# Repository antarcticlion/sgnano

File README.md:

# sgnano

**sgnano**（エスジーナノ）は、RP2350B のチップ 1 つで作る、昔ながらの操作感を持つパーソナルコンピュータです。
アナログ RGB の画面、PT8211 の 4 声ウェーブテーブル音源「Zack」、USB キーボード・マウス・ストレージを備え、
電源を入れるとファイラーが立ち上がり、その場で mruby・MicroPython・SG BASIC のプログラムを書いて走らせられます。

> いまは **α版** です。ファームウェアはバイナリ（UF2）で配り、ソースは後のリリースで公開する予定です。
> SGX の ABI は **5.x を凍結**しています（追加のみ）。文書も順次更新します。

*起動バナー。星は [`sgnano_remote`](https://github.com/antarcticlion/sgnano_remote) のアイコンです。*

## このリポジトリにあるもの

| フォルダ | 中身 |
|---|---|
| `docs/` | 3 言語のコーディングガイド、SGX の ABI、`Machine` の対応表、キー操作の早見表 |
| `samples/` | mruby・MicroPython・SG BASIC の見本（3 言語で同じものがそろったテスト用アプリ、ベンチマーク、デモ） |
| `sdk/sgx/` | C で外部実行ファイル（`.sgx`）を組むための SDK（ABI はα版の間に変わることがあります） |
| `apps/` | SGX の見本（`hello`）と CPU の計測 `cpubench`（α2 から。alpha2-2026.11.2 から 1 コア + 2 コア）。Doom と wav2mp3 のソースは別のリポジトリ（`sgnano_doomgeneric`・`sgnano_wav2mp3`） |
| `hardware/` | C ボードのガーバーと KiCad のプロジェクト（回路図・基板、α2 から） |
| `resources/bench/` | cpubench の負荷の曲（VGZ・MP3、CC BY-SA 4.0） |
| `LICENSES/` | ファームウェアと SGX に入っている外部の部品のライセンス文 |

## ハードウェア

- **CPU**: WeAct Studio RP2350B Core Board（Cortex-M33 x 2、302.4MHz で動かす）
- **メモリ**: SRAM 520KB、PSRAM 8MB、フラッシュ 16MB
- **画面**: R・G・B 各 5 ビットの R-2R ラダー DAC。15kHz / 24kHz / 31kHz の 12 通りのタイミング
- **音**: PT8211 x 4（1 チップに 1 声）。オペアンプで混ぜ、カットオフ 150kHz の LPF を通してラインアウトへ
- **入出力**: USB ホスト（フルスピード）、DIN MIDI、GPIO 8 本（PIO2 をユーザーに開放）、ADC

基板（C ボード、100 x 100mm）のガーバーと組み立てガイドは `hardware/c_board/` にあります。手はんだを前提にした高密度の実装です。

- [組み立てガイド（Markdown）](hardware/c_board/ASSEMBLY.md) / [PDF（26 ページ）](hardware/c_board/ASSEMBLY.pdf)
- [部品表（BOM）](hardware/c_board/C_BOARD_BOM.csv) / [配置（1 部品ごと）](hardware/c_board/C_BOARD_PLACEMENT.csv)

*C ボード（100 x 100mm）。RP2350B の Core Board、PT8211 x 4、DIN MIDI、VGA の DAC、GPIO のヘッダ。*

## ソフトウェア

- **ファイラー**: PC-98 の FD に倣った 2 列の一覧。テキストエディタ、日本語 IME、ZMODEM、コピー・移動
- **言語**: mruby 4.0.0、MicroPython 1.29.0、SG BASIC（3 言語の `Machine` は同じメソッドを持つ）
- **シェル**: csh のサブセット sgsh（VT220 の上位互換の端末）。OS/2 に倣うジョブ制御（`start`・`fg`・`bg`・`suspend`・`ends`・Ctrl-Z）で、同じ言語のプログラムを何本も同時に走らせられる
- **外部実行ファイル**: SGX（C で組み、PSRAM に読み込んで RTOS のタスクとして走らせる）。Core 0 にもサブタスクを起こせる（ABI 5.19）
- **画面**: テキスト面（80x30、Unicode、32 ビットの属性）・フレームバッファ（RGB555 / CLUT8 / CLUT4）・ローレゾ面（BG 2 面 + オブジェクト 128 個）
- **音**: 4 声のウェーブテーブル、SMF / SGT のシーケンサー、MP3 / OGG / WAV、VGM / VGZ（YM2151・YM2612・C352 など）

## 画面

実機の画面です（640x480。将棋・jumps・時計・CD は写真）。ほかにも `images/` にあります。

| | |
|---|---|
| <br>**ファイラー**。PC-98 の FD に倣った 2 列の一覧。 | <br>**表示の言語は 62**。欧州 34 言語を含みます。 |
| <br>**画面モード 3**。テキスト + ローレゾ + CLUT8 の FB。 | <br>**画面モード 7**。320x200x256 のプラズマとテキスト 25 行。 |
| <br>**jumps**（SGX の見本）。横スクロールのゲーム。 | <br>**フォントは 57,404 字**。色・線・回転・倍角を 1 画面で。 |
| <br>**将棋**（mruby の見本）。 | <br>**SGCALC**。mruby / MicroPython / SG BASIC のマクロ。 |
| <br>**CD のスペクトログラム**。44.1kHz ステレオ、128x128 を 2 面。 | <br>**時計**（F11）。NTP で合わせた日本時間。 |
| <br>**シェル sgsh**。csh のサブセット、組み込みコマンド 70 個。 | <br>**About**（F1 → → → →）。ビルド ID・ABI・フォント・言語数。 |

## パッチ 2（alpha2-2026.11.2）で変わったこと

前のパッチ（`alpha2-2026.11.1`、2026-11-23）から **92 のコミット**があり、内部の作りに大きく手が入っています。
新しい機能の多くは、「同じ 1 チップで、より多くを同時に、より滑らかに動かす」ための土台です。詳しくは Release のリリースノートを見てください。

### メモリ: 常駐していたコードを、使うときだけ SRAM に載せる（SRAM +32KB）

RP2350 の SRAM は 520KB しかなく、画面のライン、音、USB、言語の VM がそれを取り合います。これまでは、つながっていない機器のためのコードも
いつも SRAM に置いていました。パッチ 2 では次のコードを **使う間だけ SRAM に写して**走らせ、使い終わったら下ろします。

| まとまり | 載せるとき | 下ろすとき |
|---|---|---|
| ゲームパッド・マウス・ペンタブレット | 機器がつながったとき | 外れて 3 秒たったら |
| 光学ドライブ / FDD・ISO9660 | 光学ドライブ / FDD がつながったとき | 外れて 3 秒たったら |
| ファイラーの一部（一覧の受け口・読み込み・PNG の表示） | ファイラーが動いているとき | プログラムを走らせている間 |

- 何もつないでいないときの SRAM の空きは **173,515 B → 205,671 B（+32KB）** になりました。
- 光学ドライブ / FDD の受け場（4KB）と LAN の送受信の受け場（10.3KB）も、起動のときに取り置かず、機器がつながったときに取ります。
- SRAM が足りないときは、**フラッシュのまま遅く動きます**（止まったり壊れたりはしません）。遠隔コマンド `DYN` で、いまどこにあるかを見られます。

### 音: ドライバーも、鳴らすときだけ SRAM に

FM 音源（YM2151・OPL 系・OPN 系）、MP3 の復号、PCM 系の音源を、**曲が使うものだけ**空いた SRAM に載せるモジュールにしました。
固定の区画は 58KB → 15.9KB に縮み、音を鳴らしていないときの SRAM が大きく空きます。MP3 を鳴らしているときの負荷は **31% → 12%** になりました。
置き場は遠隔コマンド `MODS` で見られます。

### マルチタスク: Core 0 のサブタスクとジョブ制御

- SGX のプログラムが **Core 0 にもタスクを起こせます**（`task_create_core0` / `core_id`、SGX ABI 5.19）。Core 0 は画面を描く合間の空き時間で走らせます。
  3 言語にも `core_id` / `tasks` / `core_stat`。
- シェル sgsh に OS/2 風の **ジョブ制御**（`start`・`detach`・`fg`・`bg`・`suspend`・`ends`、Ctrl-Z）。mruby・MicroPython・SG BASIC のプログラムを何本も同時に走らせられます。

### 画面

- **起動バナー**を作り直しました。流れる星と回る「Ａ」を Core 0 のサブタスクで描くので、Core 1 が忙しくても止まりません。「Ａ」の 4 つのセルが別々のフレームで
  替わるティアリングと、免責の文の後ろの行が欠ける件を直しました。
- モード 2 の FB（2.4MB）を、要るときだけ取るようにしました（`fb_release` / `fb_acquire`、ABI 5.18）。シェルに入ると PSRAM へ返します。壁紙も出せます。
- SGX から 15kHz / 24kHz の画面も開けます（ABI 5.17）。
- ローレゾ面を決まった大きさ（パターン 16KB・パレット 8 本）で開く印 `SGX_MODE_LR_FIXED`（ABI 5.20）。

### 音楽 CD とプレイヤー

- 音楽 CD の再生画面の**文字のちらつきを直しました**。スペクトログラムの範囲は `r` で 1/1 → 1/2 → 1/4。
- `mplay` / `vgmplay` / ファイラーの VGM プレイヤーのスペクトログラムの直し・範囲の切り替え・周波数の目盛り・音量 200%。
- **C64 の SID の曲のプレイヤー `sidplay.sgx`**（新しい。WAV / MP3 への書き出しも）。

### そのほか

- `adcrec.sgx` が止まらなかった件、シェルの前景のプログラムへのキーの渡し方、UART のコンソールの長い行の文字落ち、Ruby のバックグラウンドのジョブを止めたときの
  HardFault などを直しました。JUMPS はパッドの上入力でもジャンプします。プログラムの実行中も画面の写し（Alt+PrintScreen）が撮れます。
- 表示の言語 62 言語の訳を直しました（キーの名前の誤訳など）。
- **SGX ABI は 5.16 → 5.20**。どれも表の末尾に足しただけで、**5.16 以前のプログラムはそのまま動きます**。

## sgnano magazine

α版を外の読者向けに紹介する読み物です。

- [第 1 号　ワンチップに「パソコン」を取り戻せ](docs/magazine/01_alpha_review.md)（2026-11-14、[誌面の PDF](docs/magazine/01_alpha_review.pdf)）
- [第 2 号　α版、出荷前夜](docs/magazine/02_alpha1_preview.md)（2026-11-17、[誌面の PDF](docs/magazine/02_alpha1_preview.pdf)）
- [第 3 号　α2、使ってみた](docs/magazine/03_alpha2_review.md)（2026-11-21、[誌面の PDF](docs/magazine/03_alpha2_review.pdf)）

## ダウンロードと書き込み

**最新リリースは [alpha2-2026.11.2](https://github.com/antarcticlion/sgnano/releases/tag/alpha2-2026.11.2) です。配布物は [Releases](https://github.com/antarcticlion/sgnano/releases) にあります。**

| 何を入れるか | ファイル |
|---|---|
| **最新ファームウェア**（S: とフォントを残して更新） | [alpha2-2026.11.2 の Release](https://github.com/antarcticlion/sgnano/releases/tag/alpha2-2026.11.2) / [ファーム UF2](https://github.com/antarcticlion/sgnano/releases/download/alpha2-2026.11.2/sgnano-alpha2-2026.11.2-firmware.uf2) |
| **S: の更新**（変わったファイル 29 本とインストーラ） | [S: の更新 zip](https://github.com/antarcticlion/sgnano/releases/download/alpha2-2026.11.2/sgnano-alpha2-2026.11.2-s-update.zip) |
| **α2 の一式**（初回。S: とフォントも入る） | [alpha2-2026.11 の Release](https://github.com/antarcticlion/sgnano/releases/tag/alpha2-2026.11) / [全体 UF2](https://github.com/antarcticlion/sgnano/releases/download/alpha2-2026.11/sgnano-alpha2-2026.11-full.uf2) / [IME の辞書](https://github.com/antarcticlion/sgnano/releases/download/alpha1-2026.11/sgnano-alpha1-2026.11-ime-dict.zip)（α1 と同じ） |
| **S: とフォント** | [後半 UF2](https://github.com/antarcticlion/sgnano/releases/download/alpha2-2026.11/sgnano-alpha2-2026.11-system-font.uf2) |

1. **初回**は α2 の全体 UF2 を、BOOTSEL で立ち上げた `RPI-RP2` へコピーします。**S: は初期化されます。**
2. そのあと、**最新ファームウェアの UF2（`alpha2-2026.11.2`）** をコピーします（ファームだけ更新。S: とフォントは残ります）。
3. **α1 や α2 から更新するとき**は、最新ファームウェアの UF2 をコピーしてください（S: とフォントはそのまま残ります）。
4. ファームを書いたら、下の手順で **S: の更新**を入れます（新しいプレイヤー・訳の直しなど。入れなくても新しいファームは動きます）。
5. 日本語の漢字変換には **IME の辞書**（`-ime-dict.zip`）が要ります。USB のドライブのルートに `SgnanoIME/` ごと置いてください（S: の 4MB には入りません）。
6. フォント ROM はファームと同じ版を使ってください。v1 の ROM では文字が出ません。

SHA-256 は各 Release の `SHA256SUMS` にあります。

### S: の更新の入れ方（alpha2-2026.11.2）

S:（内蔵フラッシュのシステムのドライブ、4MB）は空きが少ないので、**インストーラは USB メモリなどの外部のドライブに置いて使います**。
上書きする前のファイルの控えも、外部のドライブに取ります。新しいプログラムは新しいファームでないと読み込めないので、**先にファームを書いてください**。

1. `sgnano-alpha2-2026.11.2-s-update.zip` を PC で展開し、出てきた `sgnano-alpha2-2026.11.2-s-update` フォルダを丸ごと USB メモリ（FAT32・exFAT）に写します。
2. USB メモリを本体につなぎ、ファイラーでそのフォルダに入って **`install.rb` を Enter** で走らせます。
3. インストーラは次の順に進めます。
   1. 更新のファイル（S: のフォルダごとの ZIP）を USB メモリの作業フォルダへ一度展開し、大きさと CRC32 を確かめる。合わなければ何も書かずに止まる
   2. S: の空きが足りるかを確かめる
   3. **Y を押すと入れ始める**（ほかのキーでやめる）
   4. 上書きする S: のファイルを、USB メモリのそのフォルダの `backup/` に控える。控えられなければ S: に触らずに止まる
   5. S: へ入れ、入ったものの CRC32 を照らし合わせる。結果は画面と `S:/SystemLogs/install_alpha2-2026.11.2.txt` に残る
4. 入れている間は ESC を押さないでください。終わったら本体を再起動します（Shift+F12）。

**元に戻すとき**は、同じフォルダの **`restore.rb` を Enter** で走らせます。いちばん新しい控えから書き戻し、更新で新しく入ったファイルは消します。

入るもの（29 本）:

| S: のフォルダ | ファイル |
|---|---|
| `S:/bin/` | `mplay.sgx`・`vgmplay.sgx`（スペクトログラムの直しなど）、`sidplay.sgx`（新しい） |
| `S:/sbin/` | `ps.sgx`（Core 0 のタスクとコアの列） |
| `S:/SystemFiles/Locale/` | `locales.7z`（62 言語の訳の直し） |
| `S:/testapp/` | `adcrec.sgx`・`jumps.*`（5 本）・`stress.sgx`・`mode0`〜`mode6.sgx`・`mode1_vgm`〜`mode6_vgm.sgx`・`mode6_15k.sgx`・`mode6_24k.sgx`（新しい） |

## CPU の計測（cpubench、alpha2-2026.11.2）

[`apps/cpubench`](apps/cpubench/) で、画面モードと音楽の負荷の下で Dhrystone 2.1 と Linpack（n = 100）を測った結果です
（clk_sys 302.4 MHz、1 つ 5 秒、データとスタックは SRAM。2026-11-28、alpha2-2026.11.2）。かっこの中は α2（2026-11-21）の値です。

**1 コア（Core 1）**

| 画面 | 音楽 | DMIPS | 単精度 MFLOPS | 倍精度 MFLOPS | 曲の負荷 |
|---|---|---:|---:|---:|---:|
| モード 0（表示なし） | なし | 419.8（410.9） | 60.50（59.61） | 7.23（7.13） | 0% |
| モード 0 | MP3 | **350.9**（263.3） | **50.41**（39.24） | n/a（4.60） | **12%**（31%） |
| モード 0 | VGM（YM2151 + C352） | 147.9（155.0） | 24.27（24.94） | **2.73**（n/a） | 60%（57%） |
| モード 2（テキスト + RGB555 の FB） | なし | 116.2（116.8） | 16.86（16.95） | 2.00（2.02） | 0% |
| モード 2 | MP3 | **72.6**（2.2） | **10.60**（0.49） | n/a（0.00） | **21%**（111%） |
| モード 5（テキスト + ローレゾ） | なし | 416.1（410.6） | 59.97（59.56） | 7.18（7.15） | 0% |
| モード 6（ローレゾだけ） | MP3 | **347.4**（264.3） | n/a（39.41） | n/a | **12%**（31%） |
| モード 7（テキスト + 320x200 のビットマップ） | なし | **417.9**（358.1） | **60.32**（52.12） | n/a（6.55） | 0% |

**2 コア（Core 1 + Core 0 のサブタスク）**

| 画面 | 音楽 | DMIPS | 単精度 MFLOPS |
|---|---|---:|---:|
| モード 0 | なし | 669.4 | 105.61 |
| モード 6 | なし | 517.1 | 78.49 |
| モード 7 | なし | 611.1 | n/a |

- MP3 の復号が SRAM に載るモジュールになり、MP3 を鳴らしながらの計算が大きく伸びました（FB を出すモード 2 で 2.2 → 72.6 DMIPS）。
- 画面の乱れ（fifo_stall）は、全部の組み合わせで 0 でした（α2 では FB のモードで 2〜38）。
- n/a は、SRAM に必要な連続した空きが無くて測れなかった組み合わせです。MP3 の復号が SRAM を使うぶん、MP3 を鳴らしながらの倍精度は測れなくなりました。
  2 コアの倍精度は 163KB の連続した SRAM が要るので測れません。
- FB を出すモードでは、画面の取得がメモリの帯域を使うぶん遅くなります。

**サウンドフォント（SF2）は入っていません。** ファームの SMF 再生は内蔵の音源（4 声のウェーブテーブル）で鳴るので要りません。
`smf2vgm.sgx`（MIDI → VGM / VGZ）を使うときだけ、[MuseScore_General.sf2](https://ftp.osuosl.org/pub/musescore/soundfont/MuseScore_General/MuseScore_General.sf2)（約 83MB、MIT）を落として、
USB メモリの `<ドライブ>:/SoundFonts/` に置いてください（S: の 4MB には入りません）。`.sf3` は読みません。
変換した VGM / VGZ を配るときは、MuseScore General の著作権表示と MIT の許諾文を添えてください。

## 文書

入口は [`docs/README.md`](docs/README.md) です。

## 関連プロジェクト

### このプロジェクトのリポジトリ

| リポジトリ | 中身 | ライセンス |
|---|---|---|
| [`antarcticlion/sgnano`](https://github.com/antarcticlion/sgnano) | このリポジトリ。ファームのバイナリ（UF2）・文書・見本・SGX の SDK・基板データ | バイナリは無償配布、SDK と見本は MIT、文書は CC BY-SA 4.0、基板は CERN-OHL-P-2.0 |
| [`antarcticlion/EmbFont16`](https://github.com/antarcticlion/EmbFont16) | フォント ROM の形式・ビルダー（v2.0、57,404 字） | MIT（字形は GNU Unifont などのライセンス） |
| [`antarcticlion/sgnano_remote`](https://github.com/antarcticlion/sgnano_remote) | PC からファイルを管理する道具（v0.1.0。**デバッグプローブが必須**。UART の遠隔コマンドと ZMODEM で話す。起動バナーの星はこのアイコン） | MIT |
| [`antarcticlion/sgnano_doomgeneric`](https://github.com/antarcticlion/sgnano_doomgeneric) | Doom（`DOOM.SGX`。doomgeneric と Freedoom） | GPL-2.0 |
| [`antarcticlion/sgnano_wav2mp3`](https://github.com/antarcticlion/sgnano_wav2mp3) | VGM / VGZ を WAV / MP3 に書き出す `wav2mp3.sgx`（LAME） | LGPL-2.0-or-later |
| [`antarcticlion/sgnano_povray`](https://github.com/antarcticlion/sgnano_povray) | POV-Ray 3.7 の `povray.sgx`（ファームにリンクしない独立した SGX） | AGPL-3.0-or-later |

### 使っている外部のソフトウェア

| 部品 | 使い道 | ライセンス | 上流 |
|---|---|---|---|
| mruby 4.0.0 | Ruby | MIT | <https://github.com/mruby/mruby> |
| MicroPython 1.29.0 | Python | MIT | <https://github.com/micropython/micropython> |
| doomgeneric | Doom の本体 | GPL-2.0 | <https://github.com/ozkl/doomgeneric> |
| LAME 3.100 | MP3 の符号化（`wav2mp3`） | LGPL-2.0-or-later | <https://lame.sourceforge.io/> |
| Raspberry Pi Pico SDK 2.2.0 | 土台の SDK | BSD-3-Clause | <https://github.com/raspberrypi/pico-sdk> |
| TinyUSB | USB ホスト | MIT | <https://github.com/hathach/tinyusb> |
| lwIP 2.2 | TCP/IP | BSD-3-Clause | <https://savannah.nongnu.org/projects/lwip/> |
| Mbed TLS 3.6.2 | TLS 1.2・SHA | Apache-2.0 | <https://github.com/Mbed-TLS/mbedtls> |
| ymfm | VGM の FM 音源 | BSD-3-Clause | <https://github.com/aaronsgiles/ymfm> |
| libvgm | VGM の PCM 音源 | BSD-3-Clause | <https://github.com/ValleyBell/libvgm> |
| minimp3 | MP3 の解読 | CC0-1.0 | <https://github.com/lieff/minimp3> |
| stb_vorbis / stb_image | OGG の解読、PNG / JPEG / GIF の解読 | MIT / Public Domain | <https://github.com/nothings/stb> |
| miniz | gzip（VGZ）の展開 | MIT | <https://github.com/richgel999/miniz> |
| libbzip2 1.0.8 | bzip2 | BSD 系 | <https://sourceware.org/bzip2/> |
| LZMA SDK 26.06 | LZMA・xz・7z | Public Domain | <https://7-zip.org/sdk.html> |
| Onigmo 6.2.0 | Ruby の正規表現 | BSD-2-Clause | <https://github.com/k-takata/Onigmo> |
| GNU Unifont | フォントの字形 | SIL OFL 1.1 | <https://unifoundry.com/unifont/> |
| Unicode のデータ（Unihan） | IME の倉頡の表 | Unicode License V3 | <https://www.unicode.org/license.txt> |

全部の一覧とライセンス文は [`LICENSES/README.md`](LICENSES/README.md) にあります。

## 免責事項

sgnano（ファームウェア・SDK・見本・文書・基板のデータを含む）は**「現状のまま」**提供します。
明示か黙示かを問わず、商品性・特定の目的への適合性・権利を侵害していないことを含め、いかなる保証もしません。
sgnano を使ったこと、または使えなかったことによって生じたいかなる損害（データの消失、機器の故障、
ほかの機器・媒体への損害を含む）についても、作者は責任を負いません。

- α版です。ファイルの書き込みを伴う操作の前には、大切なデータのバックアップを取ってください。
- 基板の製作・改造・電源の扱いは、ご自身の責任で行ってください。
- 不具合の報告は歓迎しますが、対応や修正を約束するものではありません。

## ライセンス

詳しくは [`LICENSE`](LICENSE) を見てください。本体のファイラーで表示しているライセンスとクレジットと同じ内容も、そこに載せています。

- ファームウェアは**フリーソフトウェア**（無償で使える。バイナリの配布）として公開します。
- ファームウェアに入っている外部の部品のライセンス文は `LICENSES/` にあります。一覧は [`LICENSES/README.md`](LICENSES/README.md)。
- Doom（GPL-2.0）と wav2mp3（LGPL-2.0-or-later、LAME）のソースとビルドの手順は、別のリポジトリ [`sgnano_doomgeneric`](https://github.com/antarcticlion/sgnano_doomgeneric) と [`sgnano_wav2mp3`](https://github.com/antarcticlion/sgnano_wav2mp3) にあります。
- `samples/` の見本のプログラムは **MIT** です（`samples/LICENSE`。`neon_c/` も MIT）。`samples/sound/WTF4CH.mid` は **CC0** です（`samples/sound/LICENSE`）。
- `sdk/sgx/` は **MIT**、`apps/hello` は **CC0**、`docs/` は **CC BY-SA 4.0**、`hardware/`（ガーバー）は **CERN-OHL-P-2.0** です（それぞれのフォルダの `LICENSE`）。

---

Copyright (c) 2026 antarcticlion（南極獅子）。詳しくは [`LICENSE`](LICENSE) を見てください。

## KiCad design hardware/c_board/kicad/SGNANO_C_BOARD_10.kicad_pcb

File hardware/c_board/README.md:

# SGNANO C ボード Rev1.0

- **組み立てガイド**: [Markdown](ASSEMBLY.md) / [PDF（26 ページ）](ASSEMBLY.pdf)
- **部品表（BOM）**: [C_BOARD_BOM.csv](C_BOARD_BOM.csv)（グループ版、48 行）
- **配置**: [C_BOARD_PLACEMENT.csv](C_BOARD_PLACEMENT.csv)（1 部品ごとの基準番号・座標・面・実装方法）
- **ガーバー**: [SGNANO_C_BOARD_10.zip](SGNANO_C_BOARD_10.zip)（Rev1.0、2026-10-28 出力。シルクの `OCT/2027` は `2026-10-28` の誤植）
- **KiCad のプロジェクト**: [kicad/](kicad/)（回路図 `SGNANO_C_BOARD_10.kicad_sch`・基板 `.kicad_pcb`・プロジェクト `.kicad_pro`・配線の決まり `.rules`。題字の枠の版 R01.001、2026-11-21。α2 から）
- **ライセンス**: 基板データは CERN-OHL-P-2.0（[`../LICENSE`](../LICENSE)）。文書は CC BY-SA 4.0（[`../../docs/LICENSE`](../../docs/LICENSE)）

基板は 100 x 100mm、手はんだを前提にした高密度の実装です。対象は C ボード Rev1.0 です。

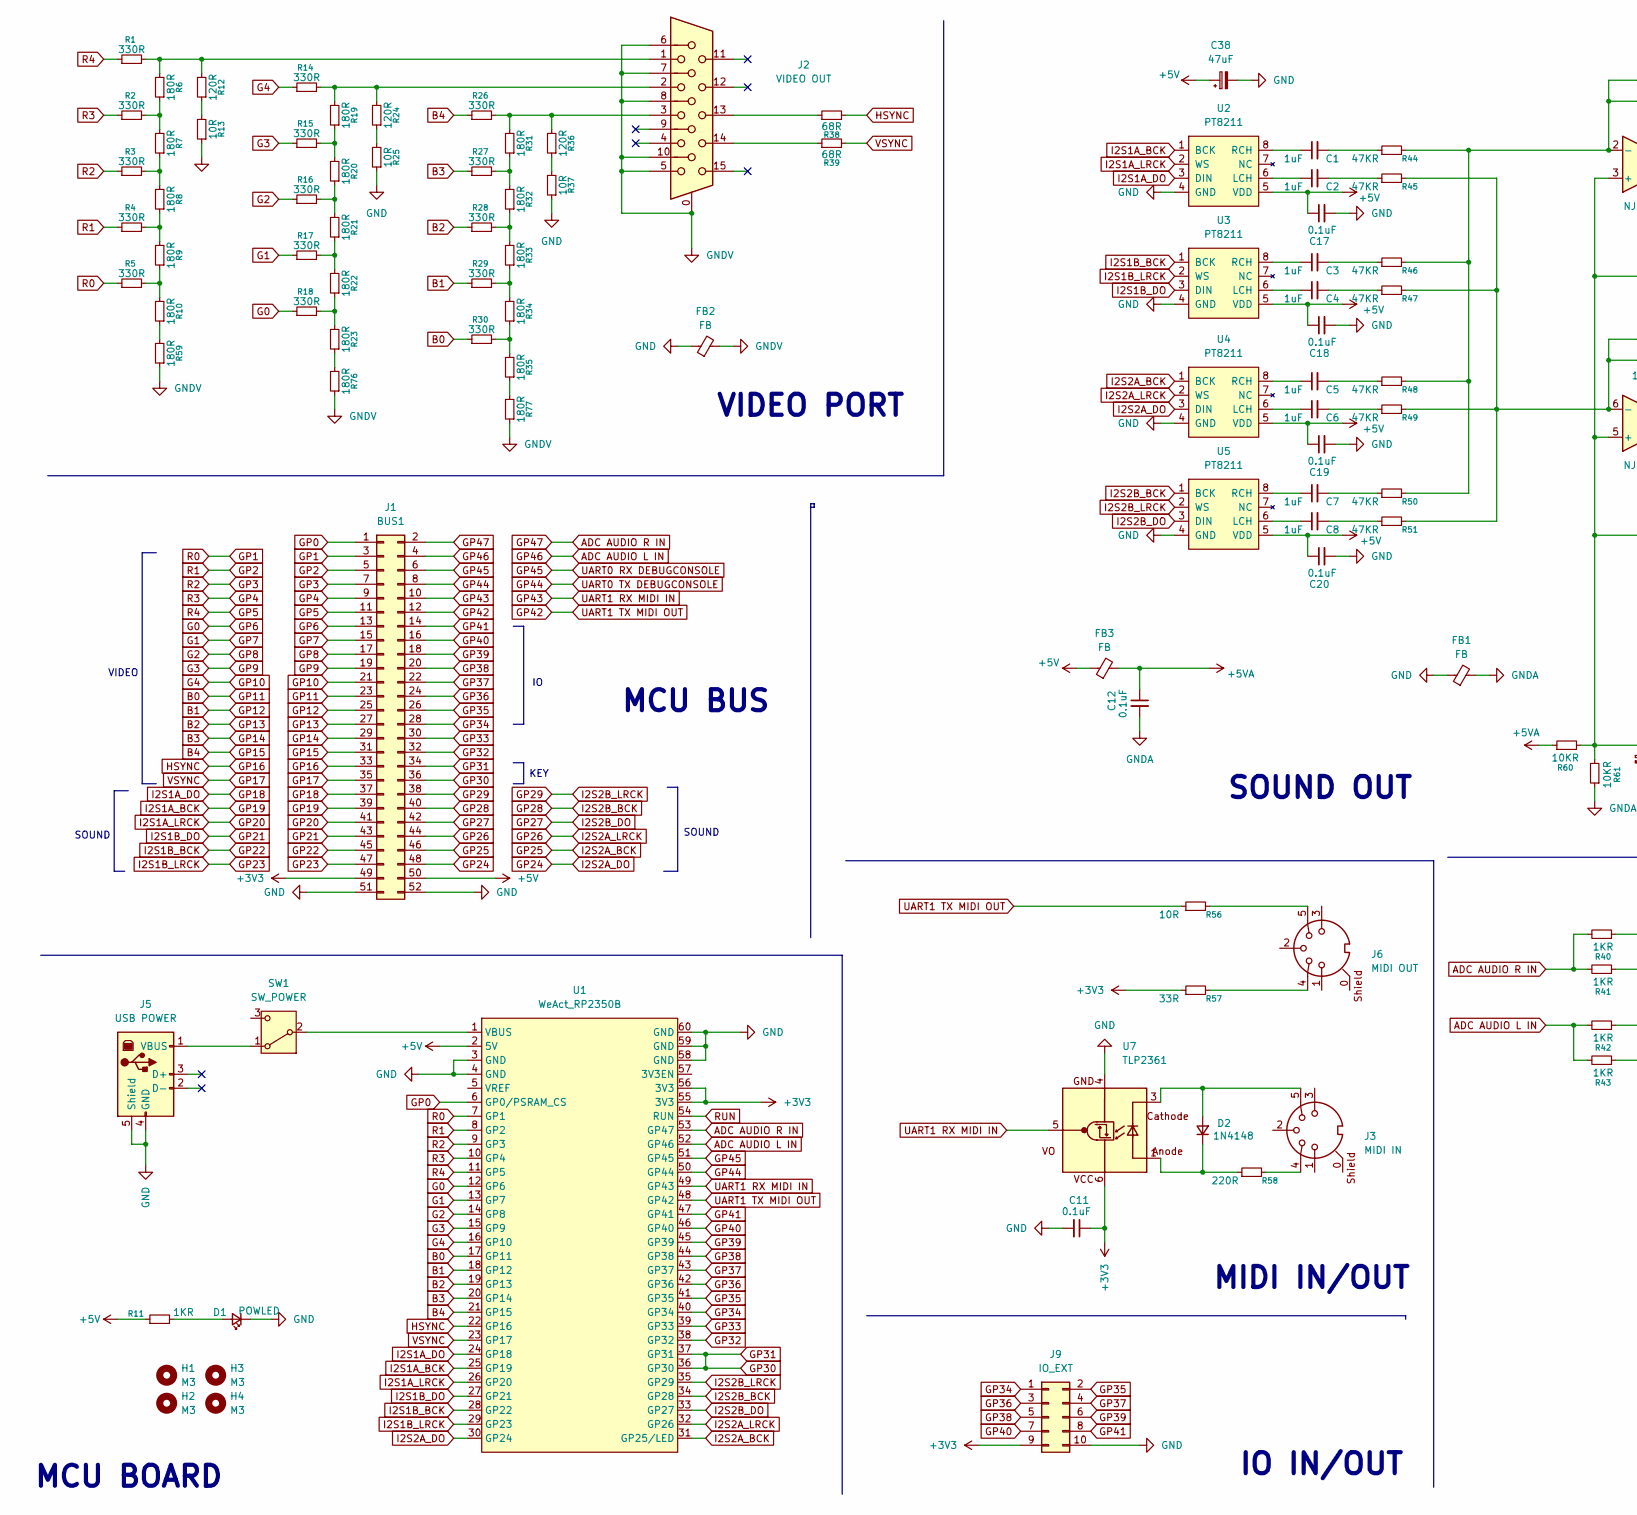
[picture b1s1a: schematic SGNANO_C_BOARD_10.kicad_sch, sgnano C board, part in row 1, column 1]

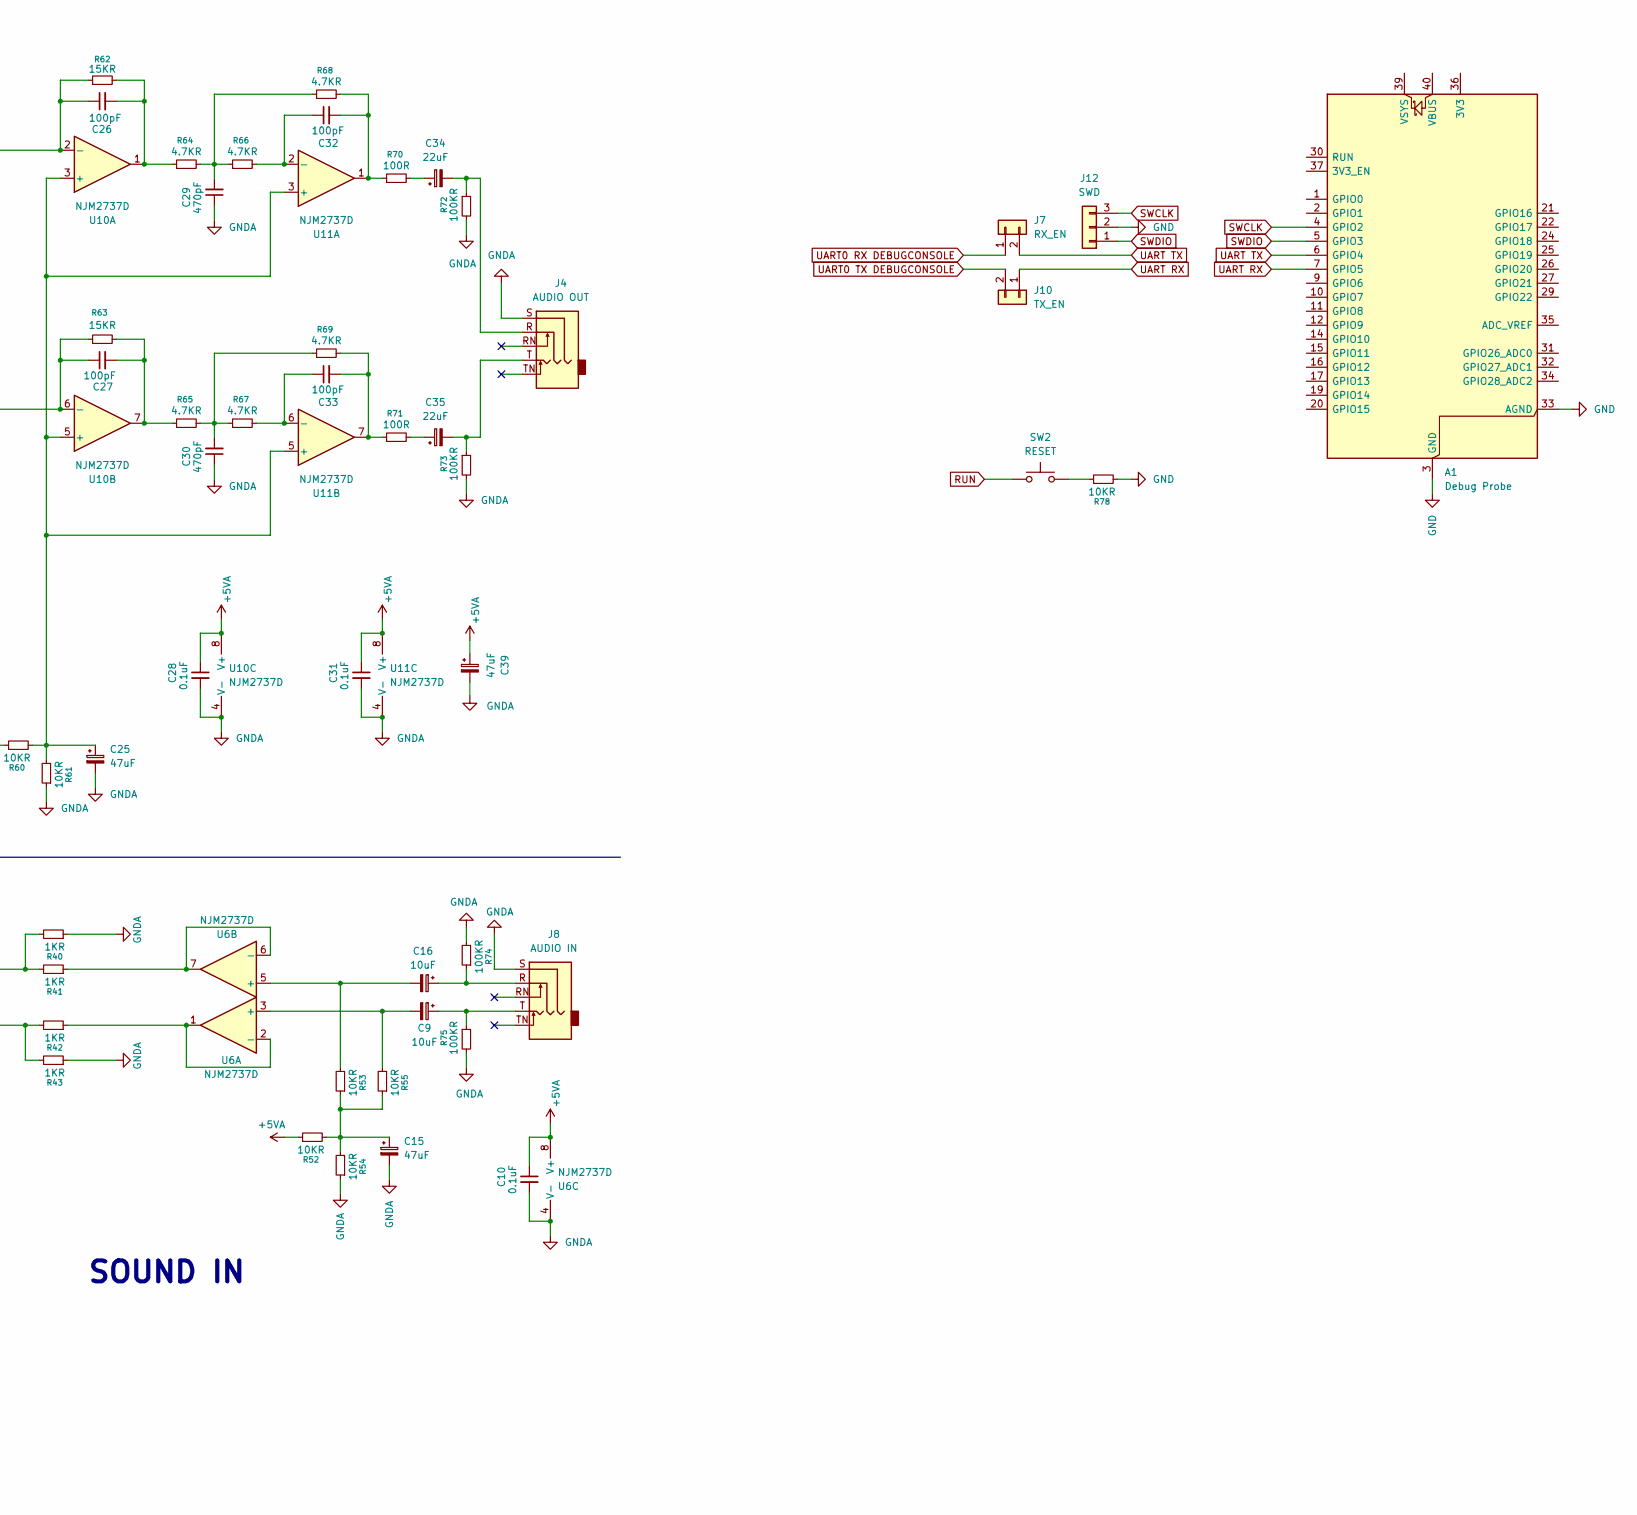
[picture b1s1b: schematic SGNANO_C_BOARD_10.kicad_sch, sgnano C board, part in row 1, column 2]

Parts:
A1: Debug Probe; RaspberryPi_Pico_Common_Unspecified
C1, C2, C3, C4, C5, C6, C7, C8: 1uF; C_Rect_L7.2mm_W5.5mm_P5.00mm_FKS2_FKP2_MKS2_MKP2
C9, C16: 10uF; CP_Radial_D5.0mm_P2.50mm
C10, C11, C12, C17, C18, C19, C20, C28, C31: 0.1uF; C_Disc_D5.0mm_W2.5mm_P5.00mm
C15, C25, C38, C39: 47uF; CP_Radial_D5.0mm_P2.50mm
C26, C27, C32, C33: 100pF; C_Disc_D5.0mm_W2.5mm_P5.00mm
C29, C30: 470pF; C_Disc_D5.0mm_W2.5mm_P5.00mm
C34, C35: 22uF; CP_Radial_D5.0mm_P2.50mm
D1: POWLED; LED_D3.0mm
D2: 1N4148; D_A-405_P7.62mm_Horizontal
FB1, FB2, FB3: FB; D_A-405_P2.54mm_Vertical_AnodeUp
H1, H2, H3, H4: M3; MountingHole_3.2mm_M3
J1: BUS1; PinHeader_2x26_P2.54mm_Vertical
J2: VIDEO OUT; DB_15F-VGA_L_NOSILK
J3: MIDI IN; DIN_8_PCB
J4: AUDIO OUT; PJ-3900-04
J5: USB POWER; USB_B_Lumberg_2411_02_Horizontal
J6: MIDI OUT; DIN_8_PCB
J7: RX_EN; PinHeader_1x02_P2.54mm_Vertical
J8: AUDIO IN; PJ-3900-04
J9: IO_EXT; IDC-Header_2x05_P2.54mm_Horizontal
J10: TX_EN; PinHeader_1x02_P2.54mm_Vertical
J12: SWD; PinHeader_1x03_P2.54mm_Vertical
R1, R2, R3, R4, R5, R14, R15, R16, R17, R18, R26, R27, R28, R29, R30: 330R; R_Axial_DIN0204_L3.6mm_D1.6mm_P2.54mm_Vertical
R6, R7, R8, R9, R10, R19, R20, R21, R22, R23, R31, R32, R33, R34, R35, R59, R76, R77: 180R; R_Axial_DIN0204_L3.6mm_D1.6mm_P2.54mm_Vertical
R11, R40, R41, R42, R43: 1KR; R_Axial_DIN0204_L3.6mm_D1.6mm_P2.54mm_Vertical
R12, R24, R36: 120R; R_Axial_DIN0204_L3.6mm_D1.6mm_P2.54mm_Vertical
R13, R25, R37, R56: 10R; R_Axial_DIN0204_L3.6mm_D1.6mm_P2.54mm_Vertical
R38, R39: 68R; R_Axial_DIN0204_L3.6mm_D1.6mm_P2.54mm_Vertical
R44, R45, R46, R47, R48, R49, R50, R51: 47KR; R_Axial_DIN0204_L3.6mm_D1.6mm_P2.54mm_Vertical
R52, R53, R54, R55, R60, R61, R78: 10KR; R_Axial_DIN0204_L3.6mm_D1.6mm_P2.54mm_Vertical
R57: 33R; R_Axial_DIN0204_L3.6mm_D1.6mm_P2.54mm_Vertical
R58: 220R; R_Axial_DIN0204_L3.6mm_D1.6mm_P2.54mm_Vertical
R62, R63: 15KR; R_Axial_DIN0204_L3.6mm_D1.6mm_P2.54mm_Vertical
R64, R65, R66, R67, R68, R69: 4.7KR; R_Axial_DIN0204_L3.6mm_D1.6mm_P2.54mm_Vertical
R70, R71: 100R; R_Axial_DIN0204_L3.6mm_D1.6mm_P2.54mm_Vertical
R72, R73, R74, R75: 100KR; R_Axial_DIN0204_L3.6mm_D1.6mm_P2.54mm_Vertical
SW1: SW_POWER; 2MS1T1B4M7QES
SW2: RESET; SW_SPST_Omron_B3F-315x_Angled
U1: WeAct_RP2350B
U2, U3, U4, U5: PT8211; SOP-8_3.9x4.9mm_P1.27mm
U6, U10, U11: NJM2737D; DIP-8_W7.62mm_Socket
U7: TLP2361; SO-5_4.4x3.6mm_P1.27mm

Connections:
+3V3: C11.1, J1.49, J9.9, R57.1, U1.55 (3V3), U1.56 (3V3), U7.6 (VDD)
+5V: C17.1, C18.1, C19.1, C20.1, C38.1, FB3.1, J1.50, R11.1, U1.2 (5V), U2.5 (VDD), U3.5 (VDD), U4.5 (VDD), U5.5 (VDD)
+5VA: C10.1, C12.1, C28.1, C31.1, C39.1, FB3.2, R52.1, R60.1, U6.8 (V+), U10.8 (V+), U11.8 (V+)
ADC AUDIO L IN: J1.4, R42.2, R43.2, U1.52 (GP46)
ADC AUDIO R IN: J1.2, R40.2, R41.2, U1.53 (GP47)
B0: J1.23, R30.1, U1.17 (GP11)
B1: J1.25, R29.1, U1.18 (GP12)
B2: J1.27, R28.1, U1.19 (GP13)
B3: J1.29, R27.1, U1.20 (GP14)
B4: J1.31, R26.1, U1.21 (GP15)
G0: J1.13, R18.1, U1.12 (GP6)
G1: J1.15, R17.1, U1.13 (GP7)
G2: J1.17, R16.1, U1.14 (GP8)
G3: J1.19, R15.1, U1.15 (GP9)
G4: J1.21, R14.1, U1.16 (GP10)
GND: A1.3 (GND), A1.8 (GND), A1.13 (GND), A1.18 (GND), A1.23 (GND), A1.28 (GND), A1.33 (AGND), A1.38 (GND), C11.2, C17.2, C18.2, C19.2, C20.2, C38.2, D1.1 (K), FB1.1, FB2.1, J1.51, J1.52, J5.4 (GND), J5.5 (Shield), J9.10, J12.2, R13.1, R25.1, R37.1, R78.2, U1.3 (GND), U1.4 (GND), U1.58 (GND), U1.59 (GND), U1.60 (GND), U2.4 (GND), U3.4 (GND), U4.4 (GND), U5.4 (GND), U7.4 (GND)
GNDA: C10.2, C12.2, C15.2, C25.2, C28.2, C29.1, C30.1, C31.2, C39.2, FB1.2, J4.S, J8.S, R40.1, R43.1, R54.1, R61.1, R72.2, R73.2, R74.2, R75.2, U6.4 (V-), U10.4 (V-), U11.4 (V-)
GNDV: FB2.2, J2.0, J2.5, J2.6, J2.7, J2.8, J2.10, R59.1, R76.1, R77.1
GP0: J1.1, U1.6 (GP0/PSRAM_CS)
GP1: J1.3, R5.1, U1.7 (GP1)
GP2: J1.5, R4.1, U1.8 (GP2)
GP3: J1.7, R3.1, U1.9 (GP3)
GP4: J1.9, R2.1, U1.10 (GP4)
GP5: J1.11, R1.1, U1.11 (GP5)
GP16: J1.33, R38.2, U1.22 (GP16)
GP17: J1.35, R39.2, U1.23 (GP17)
GP18: J1.37, U1.24 (GP18), U2.3 (DIN)
GP19: J1.39, U1.25 (GP19), U2.1 (BCK)
GP20: J1.41, U1.26 (GP20), U2.2 (WS)
GP21: J1.43, U1.27 (GP21), U3.3 (DIN)
GP22: J1.45, U1.28 (GP22), U3.1 (BCK)
GP23: J1.47, U1.29 (GP23), U3.2 (WS)
GP24: J1.48, U1.30 (GP24), U4.3 (DIN)
GP25: J1.46, U1.31 (GP25/LED), U4.1 (BCK)
GP26: J1.44, U1.32 (GP26), U4.2 (WS)
GP27: J1.42, U1.33 (GP27), U5.3 (DIN)
GP28: J1.40, U1.34 (GP28), U5.1 (BCK)
GP29: J1.38, U1.35 (GP29), U5.2 (WS)
GP30: J1.34, J1.36, U1.36 (GP30), U1.37 (GP31)
GP32: J1.32, U1.38 (GP32)
GP33: J1.30, U1.39 (GP33)
GP34: J1.28, J9.1, U1.40 (GP34)
GP35: J1.26, J9.2, U1.41 (GP35)
GP36: J1.24, J9.3, U1.42 (GP36)
GP37: J1.22, J9.4, U1.43 (GP37)
GP38: J1.20, J9.5, U1.44 (GP38)
GP39: J1.18, J9.6, U1.45 (GP39)
GP40: J1.16, J9.7, U1.46 (GP40)
GP41: J1.14, J9.8, U1.47 (GP41)
GP42: J1.12, R56.1, U1.48 (GP42)
GP43: J1.10, U1.49 (GP43), U7.5 (VO)
GP44: J1.8, J10.2, U1.50 (GP44)
GP45: J1.6, J7.1, U1.51 (GP45)
unnamed: C1.2, R44.1
unnamed: C2.2, R45.1
unnamed: C3.2, R46.1
unnamed: C4.2, R47.1
unnamed: C5.2, R48.1
unnamed: C6.2, R49.1
unnamed: C7.2, R50.1
unnamed: C8.2, R51.1
unnamed: C9.1, J8.T, R75.1
unnamed: C15.1, R52.2, R53.1, R54.2, R55.1
unnamed: C16.1, J8.R, R74.1
unnamed: C26.2, R62.2, R64.1, U10.1
unnamed: C27.2, R63.2, R65.1, U10.7
unnamed: C29.2, R64.2, R66.1, R68.1
unnamed: C30.2, R65.2, R67.1, R69.1
unnamed: C32.2, R68.2, R70.1, U11.1
unnamed: C33.2, R69.2, R71.1, U11.7
unnamed: C34.1, R70.2
unnamed: C34.2, J4.R, R72.1
unnamed: C35.1, R71.2
unnamed: C35.2, J4.T, R73.1
unnamed: D1.2 (A), R11.2
unnamed: D2.2 (A), J3.5, U7.3 (K)
unnamed: D2.1 (K), R58.1, U7.1 (A)
unnamed: J2.1, R1.2, R6.2, R12.2
unnamed: J2.2, R14.2, R19.2, R24.2
unnamed: J2.3, R26.2, R31.2, R36.2
unnamed: J2.13, R38.1
unnamed: J2.14, R39.1
unnamed: J3.4, R58.2
unnamed: J5.1 (VBUS), SW1.1 (A)
unnamed: J6.4, R57.2
unnamed: J6.5, R56.2
unnamed: R2.2, R6.1, R7.2
unnamed: R3.2, R7.1, R8.2
unnamed: R4.2, R8.1, R9.2
unnamed: R10.1, R59.2
unnamed: R5.2, R9.1, R10.2
unnamed: R12.1, R13.2
unnamed: R15.2, R19.1, R20.2
unnamed: R16.2, R20.1, R21.2
unnamed: R17.2, R21.1, R22.2
unnamed: R18.2, R22.1, R23.2
unnamed: R23.1, R76.2
unnamed: R24.1, R25.2
unnamed: R27.2, R31.1, R32.2
unnamed: R28.2, R32.1, R33.2
unnamed: R29.2, R33.1, R34.2
unnamed: R30.2, R34.1, R35.2
unnamed: R35.1, R77.2
unnamed: R36.1, R37.2
unnamed: R78.1, SW2.2
unnamed: SW1.2 (B), U1.1 (VBUS)
unnamed: C2.1, U2.6 (LCH)
unnamed: C1.1, U2.8 (RCH)
unnamed: C4.1, U3.6 (LCH)
unnamed: C3.1, U3.8 (RCH)
unnamed: C6.1, U4.6 (LCH)
unnamed: C5.1, U4.8 (RCH)
unnamed: C8.1, U5.6 (LCH)
unnamed: C7.1, U5.8 (RCH)
unnamed: C9.2, R55.2, U6.3 (+)
unnamed: R42.1, U6.1, U6.2 (-)
unnamed: C16.2, R53.2, U6.5 (+)
unnamed: R41.1, U6.6 (-), U6.7
unnamed: C25.1, R60.2, R61.2, U10.3 (+), U10.5 (+), U11.3 (+), U11.5 (+)
unnamed: C26.1, R44.2, R46.2, R48.2, R50.2, R62.1, U10.2 (-)
unnamed: C27.1, R45.2, R47.2, R49.2, R51.2, R63.1, U10.6 (-)
unnamed: C32.1, R66.2, U11.2 (-)
unnamed: C33.1, R67.2, U11.6 (-)
RUN: SW2.1, U1.54 (RUN)
SWCLK: A1.4 (GPIO2), J12.3
SWDIO: A1.5 (GPIO3), J12.1
UART RX: A1.7 (GPIO5), J10.1
UART TX: A1.6 (GPIO4), J7.2

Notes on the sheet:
SOUND OUT
VIDEO
MCU BOARD
IO IN/OUT
SOUND
KEY
MIDI IN/OUT
MCU BUS
SOUND IN
VIDEO PORT

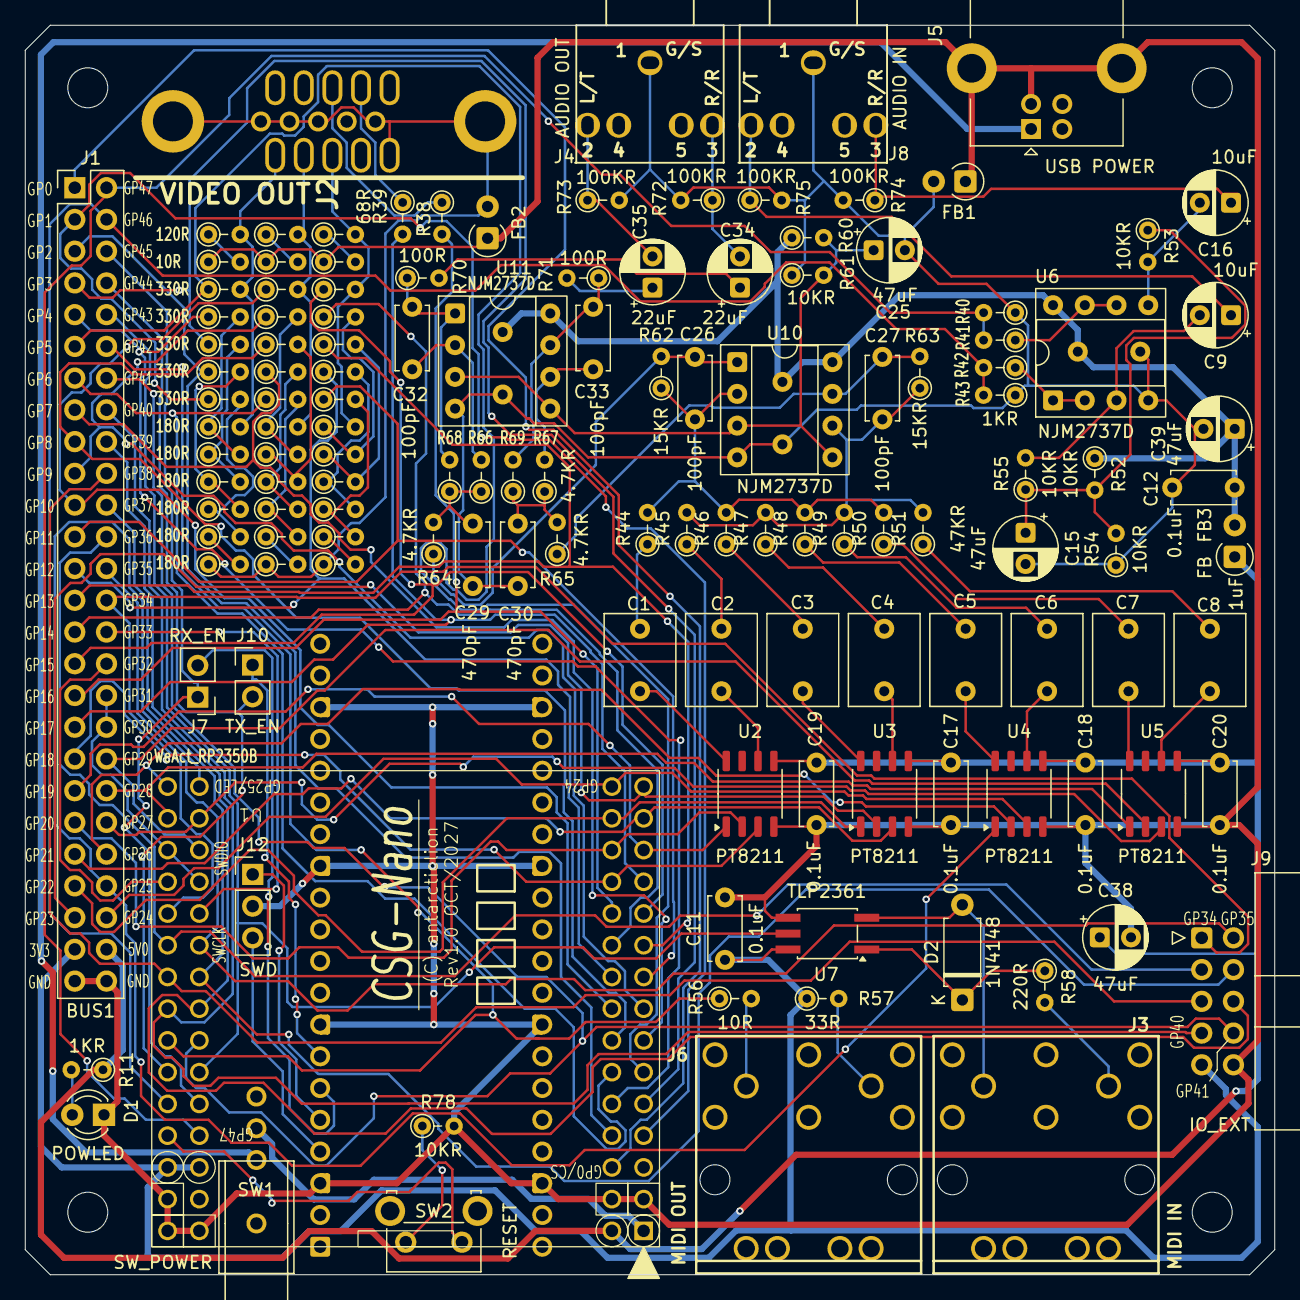
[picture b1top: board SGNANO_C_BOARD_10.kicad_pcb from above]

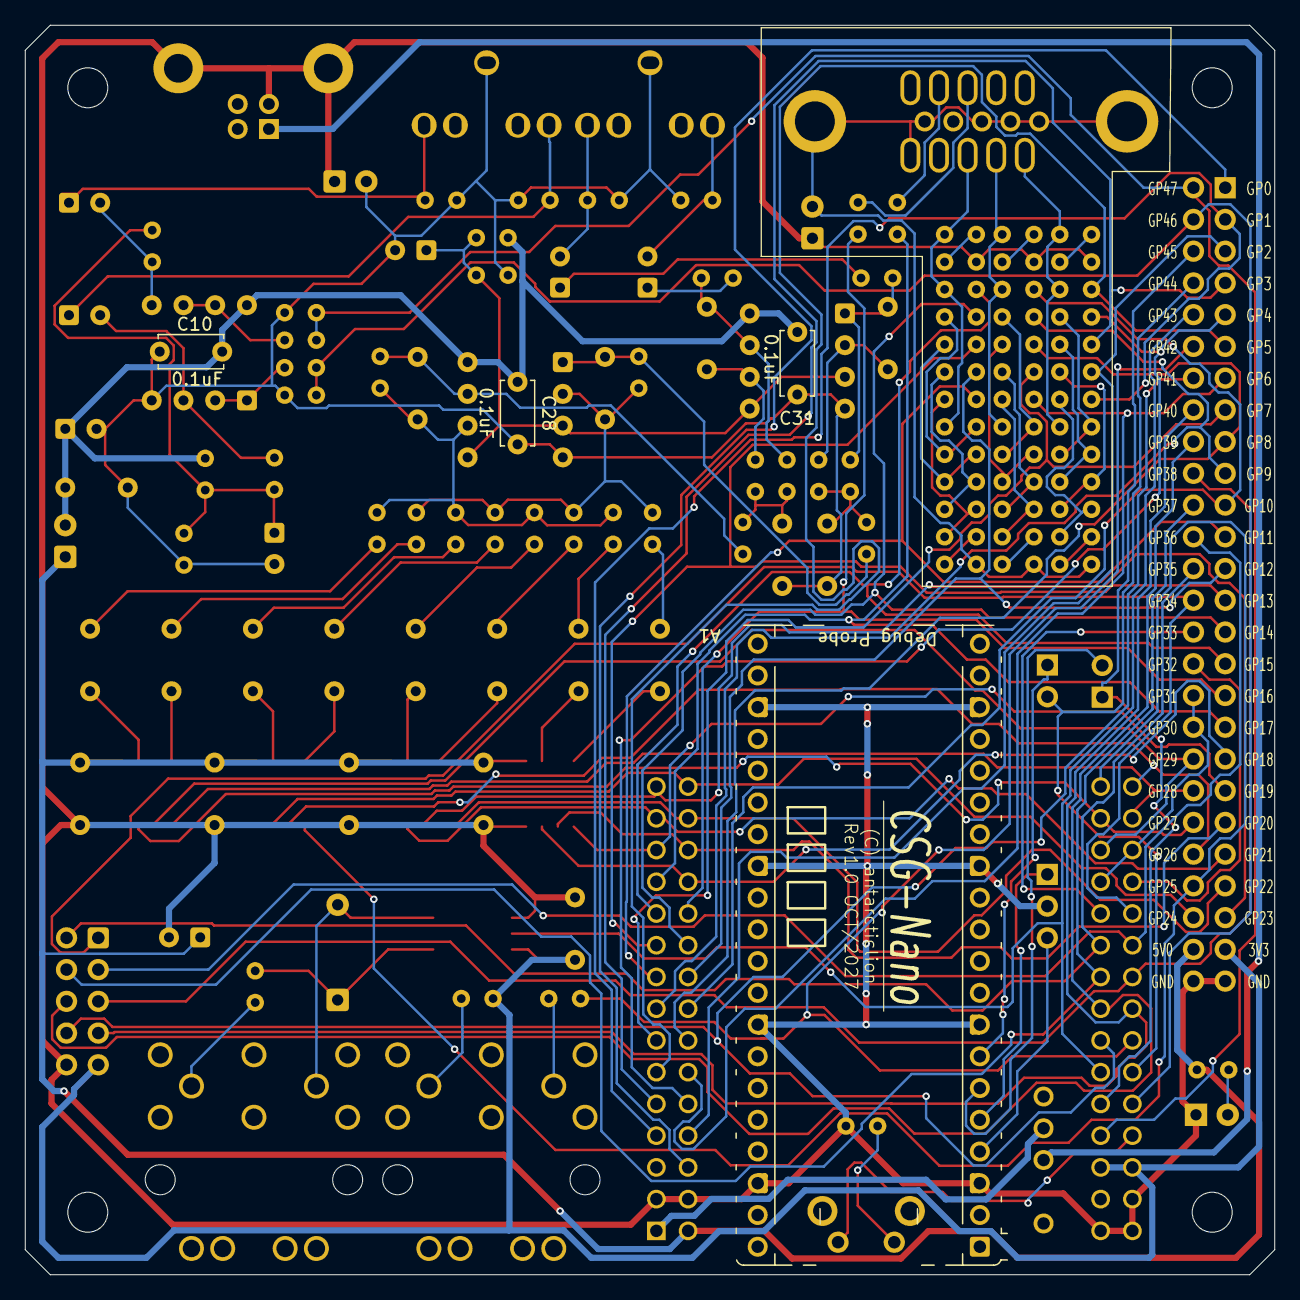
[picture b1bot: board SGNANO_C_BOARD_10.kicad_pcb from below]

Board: 2 copper layers, 100.0 x 100.0 mm, 141 parts (4 on the bottom side), 128 nets.

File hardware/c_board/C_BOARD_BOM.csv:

No,Category,Value,Qty,References,Spec,Package,Side,Mounting,Candidate,Notes
1,モジュール,WeAct RP2350B Core Board,1,U1,16MB Flash / PSRAM未搭載（ESP-PSRAM64Hを追加） / RP2350B / 2x30 2.54mm,2x30 ピンモジュール,F,THT,WeAct Studio RP2350B Core Board,PSRAMは別途ESP-PSRAM64Hを裏面に実装。ユーザースイッチのプルアップ抵抗を除去。2x30ピンソケット推奨。USB-Cは下辺（MIDI側）
2,IC,PT8211,4,"U2,U3,U4,U5",16bit DAC / SOP-8 / 1.27mmピッチ,SOP-8 3.9x4.9mm,F,SMD,PT8211-S,4声分。ピン1の三角マークとパッケージのドットを合わせる
3,IC,NJM2737D,3,"U6,U10,U11",デュアルオペアンプ / DIP-8 / 7.62mm幅,DIP-8,F,THT,NJM2737D,DIP-8ソケット使用。ノッチとピン1を合わせる
4,IC,TLP2361,1,U7,フォトカプラ / SO-5 / 1.27mmピッチ,SO-5 4.4x3.6mm,F,SMD,"TLP2361(TPL,E)",MIDI IN用。ピン2は無い。ピン1の三角マーク注意
5,LED,POWLED,1,D1,3mm赤色LED / 電源表示,LED_D3.0mm,F,THT,L-53SRD など,長脚=アノード(+)、短脚=カソード(-)。逆付け注意
6,ダイオード,1N4148,1,D2,小信号ダイオード / DO-35 / 7.62mmピッチ,DO-35 軸形,F,THT,1N4148,帯=カソード。シルクのKに合わせる
7,抵抗,330Ω,15,"R1,R2,R3,R4,R5,R14,R15,R16,R17,R18,R26,R27,R28,R29,R30",1/4W 1% 金属皮膜 / 軸形 / 縦実装,R_Axial_DIN0204 縦,F,THT,Yageo MFR-25FBF52-330R,VGA R/G/Bの各5本。33Ωと混同注意
8,抵抗,180Ω,18,"R6,R7,R8,R9,R10,R19,R20,R21,R22,R23,R31,R32,R33,R34,R35,R59,R76,R77",1/4W 1% 金属皮膜 / 軸形 / 縦実装,R_Axial_DIN0204 縦,F,THT,Yageo MFR-25FBF52-180R,VGAラダー15本＋終端3本（R59/R76/R77）
9,抵抗,120Ω,3,"R12,R24,R36",1/4W 1% 金属皮膜 / 軸形 / 縦実装,R_Axial_DIN0204 縦,F,THT,Yageo MFR-25FBF52-120R,VGA出力の直列抵抗
10,抵抗,10Ω,4,"R13,R25,R37,R56",1/4W 1% 金属皮膜 / 軸形 / 縦実装,R_Axial_DIN0204 縦,F,THT,Yageo MFR-25FBF52-10R,R13/R25/R37=VGA終端、R56=MIDI OUT
11,抵抗,68Ω,2,"R38,R39",1/4W 1% 金属皮膜 / 軸形 / 縦実装,R_Axial_DIN0204 縦,F,THT,Yageo MFR-25FBF52-68R,HSYNC / VSYNC
12,抵抗,47kΩ,8,"R44,R45,R46,R47,R48,R49,R50,R51",1/4W 1% 金属皮膜 / 軸形 / 縦実装,R_Axial_DIN0204 縦,F,THT,Yageo MFR-25FBF52-47K,オーディオミキサ入力。4声×L/Rの8本
13,抵抗,15kΩ,2,"R62,R63",1/4W 1% 金属皮膜 / 軸形 / 縦実装,R_Axial_DIN0204 縦,F,THT,Yageo MFR-25FBF52-15K,ミキサの帰還抵抗
14,抵抗,4.7kΩ,6,"R64,R65,R66,R67,R68,R69",1/4W 1% 金属皮膜 / 軸形 / 縦実装,R_Axial_DIN0204 縦,F,THT,Yageo MFR-25FBF52-4K7,オーディオLPF
15,抵抗,100Ω,2,"R70,R71",1/4W 1% 金属皮膜 / 軸形 / 縦実装,R_Axial_DIN0204 縦,F,THT,Yageo MFR-25FBF52-100R,オーディオ出力の直列抵抗
16,抵抗,1kΩ,5,"R11,R40,R41,R42,R43",1/4W 1% 金属皮膜 / 軸形 / 縦実装,R_Axial_DIN0204 縦,F,THT,Yageo MFR-25FBF52-1K,R11=LED、R40-R43=ADC入力/オーディオ入力
17,抵抗,10kΩ,7,"R52,R53,R54,R55,R60,R61,R78",1/4W 1% 金属皮膜 / 軸形 / 縦実装,R_Axial_DIN0204 縦,F,THT,Yageo MFR-25FBF52-10K,バイアス、リセット、オーディオ入力
18,抵抗,100kΩ,4,"R72,R73,R74,R75",1/4W 1% 金属皮膜 / 軸形 / 縦実装,R_Axial_DIN0204 縦,F,THT,Yageo MFR-25FBF52-100K,オーディオ入力のバイアス
19,抵抗,220Ω,1,R58,1/4W 1% 金属皮膜 / 軸形 / 縦実装,R_Axial_DIN0204 縦,F,THT,Yageo MFR-25FBF52-220R,MIDI INの電流制限
20,抵抗,33Ω,1,R57,1/4W 1% 金属皮膜 / 軸形 / 縦実装,R_Axial_DIN0204 縦,F,THT,Yageo MFR-25FBF52-33R,MIDI OUTの+3V3側
21,コンデンサ,1µF,8,"C1,C2,C3,C4,C5,C6,C7,C8",5mmピッチ 積層フィルム / 7.2x5.5mm / 50V以上,C_Rect 5mm,F,THT,WIMA MKS2 1µF/50V など / C0G MLCC可,極性なし。オーディオ結合。C1-C8。C0G MLCC可
22,コンデンサ,0.1µF,9,"C10,C11,C12,C17,C18,C19,C20,C28,C31",5mmピッチ セラミックディスク / 50V / X7R,C_Disc 5mm,B/F,THT,50V X7R ディスク,C10/C28/C31は裏面。デカップリング
23,コンデンサ,100pF,4,"C26,C27,C32,C33",5mmピッチ フィルム / 50V以上,5mmピッチ,F,THT,WIMA FKP2 100pF/100V など / C0G MLCC可,オーディオLPF。C0G MLCC可
24,コンデンサ,470pF,2,"C29,C30",5mmピッチ フィルム / 50V以上,5mmピッチ,F,THT,WIMA FKP2 470pF/100V など / C0G MLCC可,オーディオLPF。C0G MLCC可
25,コンデンサ,10µF,2,"C9,C16",5mm径 / 2.5mmピッチ / 25V以上,CP_Radial 5mm,F,THT,Rubycon 25YXJ10M5X11 など,極性あり。+は長脚
26,コンデンサ,22µF,2,"C34,C35",5mm径 / 2.5mmピッチ / 25V以上,CP_Radial 5mm,F,THT,Rubycon 25YXJ22M5X11 など,極性あり。オーディオ出力の結合
27,コンデンサ,47µF,4,"C15,C25,C38,C39",5mm径 / 2.5mmピッチ / 25V以上,CP_Radial 5mm,F,THT,Rubycon 25YXJ47M5X11 など,極性あり。電源/バイアス
28,コネクタ,BUS1 (2x26),1,J1,2x26 / 2.54mm / 垂直 / オス,PinHeader 2x26,F,THT,2x26 2.54mm ピンヘッダ,ピン1は四角パッド。左辺に実装
29,コネクタ,VIDEO OUT (VGA),1,J2,DB-15F 高密度3列 / 右アングル / 15pin,DB-15F,F,THT,DB-15F 高密度 基板取付,上辺に実装。DDC/EDIDは未接続
30,コネクタ,MIDI IN,1,J3,DIN 5pin 180° / 基板取付 / シールド付,DIN_8_PCB,F,THT,DIN-5 180° 基板取付,下辺に実装。信号はピン4/5。ピン2はNC
31,コネクタ,MIDI OUT,1,J6,DIN 5pin 180° / 基板取付 / シールド付,DIN_8_PCB,F,THT,DIN-5 180° 基板取付,下辺に実装。信号はピン4/5。ピン2はNC
32,コネクタ,AUDIO OUT,1,J4,3.5mmステレオジャック / スイッチ付,PJ-3900-04,F,THT,PJ-3900-04,上辺に実装。T=L、R=R、S=GNDA。ライン出力
33,コネクタ,AUDIO IN,1,J8,3.5mmステレオジャック / スイッチ付,PJ-3900-04,F,THT,PJ-3900-04,上辺に実装。T=L、R=R、S=GNDA。ライン入力
34,コネクタ,USB POWER,1,J5,USB B 水平 / Lumberg 2411 02,USB_B horizontal,F,THT,Lumberg 2411 02,上辺に実装。電源専用。D-/D+はNC
35,コネクタ,RX_EN,1,J7,1x2 / 2.54mm / 垂直,PinHeader 1x2,F,THT,2.54mm ピンヘッダ,A1使用時にジャンパ。GP45とA1 UART TX
36,コネクタ,TX_EN,1,J10,1x2 / 2.54mm / 垂直,PinHeader 1x2,F,THT,2.54mm ピンヘッダ,A1使用時にジャンパ。GP44とA1 UART RX
37,コネクタ,IO_EXT,1,J9,2x5 / 2.54mm / 横型 IDC,IDC-Header 2x5,F,THT,2x5 IDC ボックスヘッダ,右辺に実装。ピン1は四角パッド
38,コネクタ,SWD,1,J12,1x3 / 2.54mm / Lアングル（右アングル）,PinHeader 1x3 Lアングル,F,THT,2.54mm Lアングルピンヘッダ,1=SWDIO、2=GND、3=SWCLK。A1の上にカプトンテープを貼ってから実装
39,スイッチ,SW_POWER,1,SW1,SPDT スライドスイッチ / 2MS1T1B4M7QES,2MS1T1B4M7QES,F,THT,2MS1T1B4M7QES,下辺に実装。USB 5Vを入切
40,スイッチ,RESET,1,SW2,右アングル tactスイッチ / Omron B3F-315x,B3F-315x,F,THT,Omron B3F-3150/3152,下辺に実装。高さ/向きを確認
41,フェライトビーズ,BL01RN1A1D2,3,"FB1,FB2,FB3",軸形 / 3.4〜3.6mm / 7A / 65Ω@100MHz,D_A-405 縦,F,THT,Murata BL01RN1A1D2（秋月 129357） / 代替 BL01RN1A2A2B,ダイオードと同形。FBを入れ間違えない。代替はリード間隔を2.54mmに曲げる
42,モジュール（任意）,Debug Probe,1,A1,Raspberry Pi Pico / Pico 2 / 2x20,Pico 2x20,B,THT,Raspberry Pi Pico / Pico 2,"任意実装。最新版debugprobe推奨。3V3は基板と未接続。自前のUSB給電。SWDはWeActとGND位置が違う（J12: 1=SWDIO, 2=GND, 3=SWCLK）"
43,機構部品,M3 ネジ/スペーサー,4,"H1,H2,H3,H4",M3 / 3.2mm穴 / 長さは実装に合わせる,M3,F,THT,M3,4箇所。基板厚1.6mm
44,ソケット,DIP-8 ソケット,3,"U6,U10,U11",8pin / 2.54mm / 7.62mm幅,DIP-8,F,THT,8P DIPソケット,NJM2737D用。3個
45,ソケット,2x30 ピンソケット,1,U1,2x30 / 2.54mm / 女性,2x30,F,THT,2x30 2.54mm ピンソケット,U1用。1個。直接はんだ付けも可
46,ソケット（任意）,2x20 ピンソケット,1,A1,2x20 / 2.54mm / 女性,2x20,B,THT,2x20 2.54mm ピンソケット,A1用。任意
47,ジャンパ,2.54mm ジャンパ,2,"J7,J10",2.54mm / シャント,2.54mm,F,THT,2.54mm ジャンパシャント,A1使用時に2個
48,モジュール付属,ESP-PSRAM64H,1,U1 (裏面),64Mbit = 8MB / SOP-8,SOP-8,B,SMD,ESP-PSRAM64H,U1はPSRAM未搭載。裏面に実装。向き注意。SMDリワーク
